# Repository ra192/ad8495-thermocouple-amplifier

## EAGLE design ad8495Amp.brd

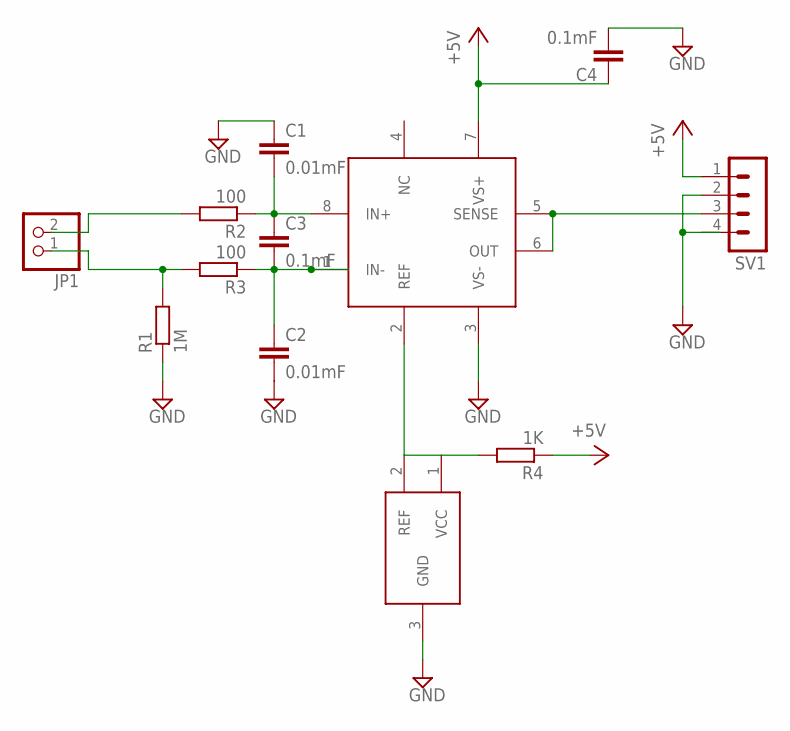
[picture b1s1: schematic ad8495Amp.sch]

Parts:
C1, C2: 0.01mF; C1206
C3, C4: 0.1mF; C1206
JP1: PINHD-1X2; 1X02
R1: 1M; R1206
R2, R3: 100; R1206
R4: 1K; R1206
SV1: MA04-1
U$1: AD8495MSOP8; MSOP8
U$2: TLVH431TLVH431; SOT23-R

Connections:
+5V: C4.1, R4.1, SV1.1, U$1.7 (VS+)
GND: C1.1, C2.2, C4.2, R1.1, SV1.2, U$1.3 (VS-), U$2.3 (GND)
unnamed: C2.1, C3.2, R3.1, U$1.1 (IN-)
unnamed: C1.2, C3.1, R2.1, U$1.8 (IN+)
unnamed: SV1.3, U$1.5 (SENSE), U$1.6 (OUT)
unnamed: JP1.2, R2.2
unnamed: R4.2, U$1.2 (REF), U$2.1 (VCC), U$2.2 (REF)
unnamed: JP1.1, R1.2, R3.2

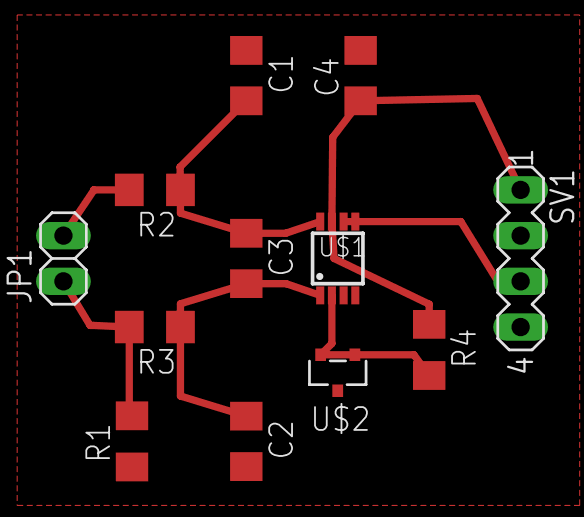
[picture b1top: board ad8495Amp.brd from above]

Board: 2 copper layers, 12 parts (0 on the bottom side), 8 nets.
